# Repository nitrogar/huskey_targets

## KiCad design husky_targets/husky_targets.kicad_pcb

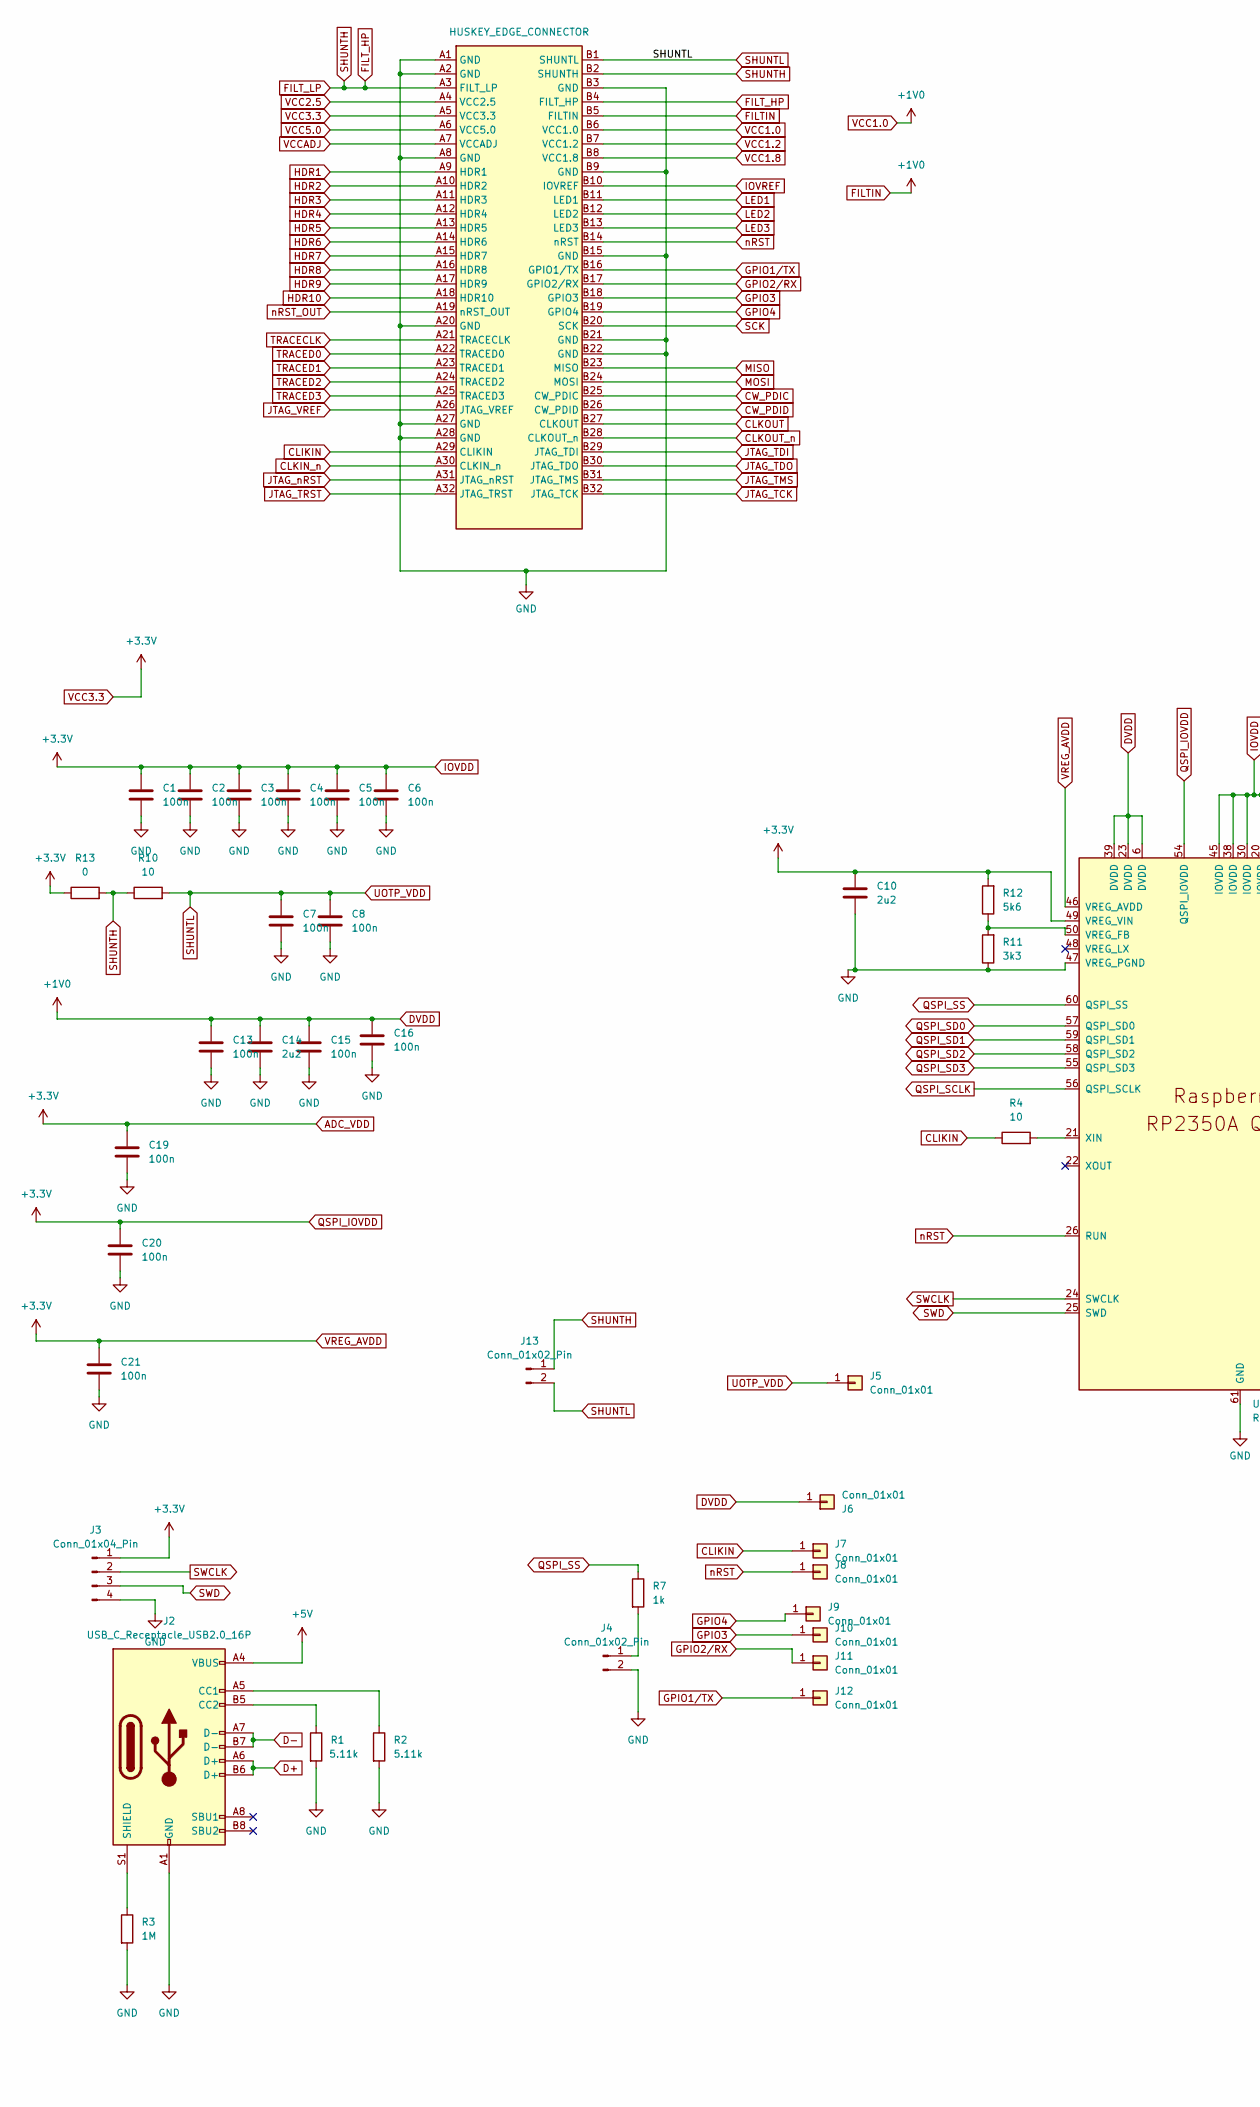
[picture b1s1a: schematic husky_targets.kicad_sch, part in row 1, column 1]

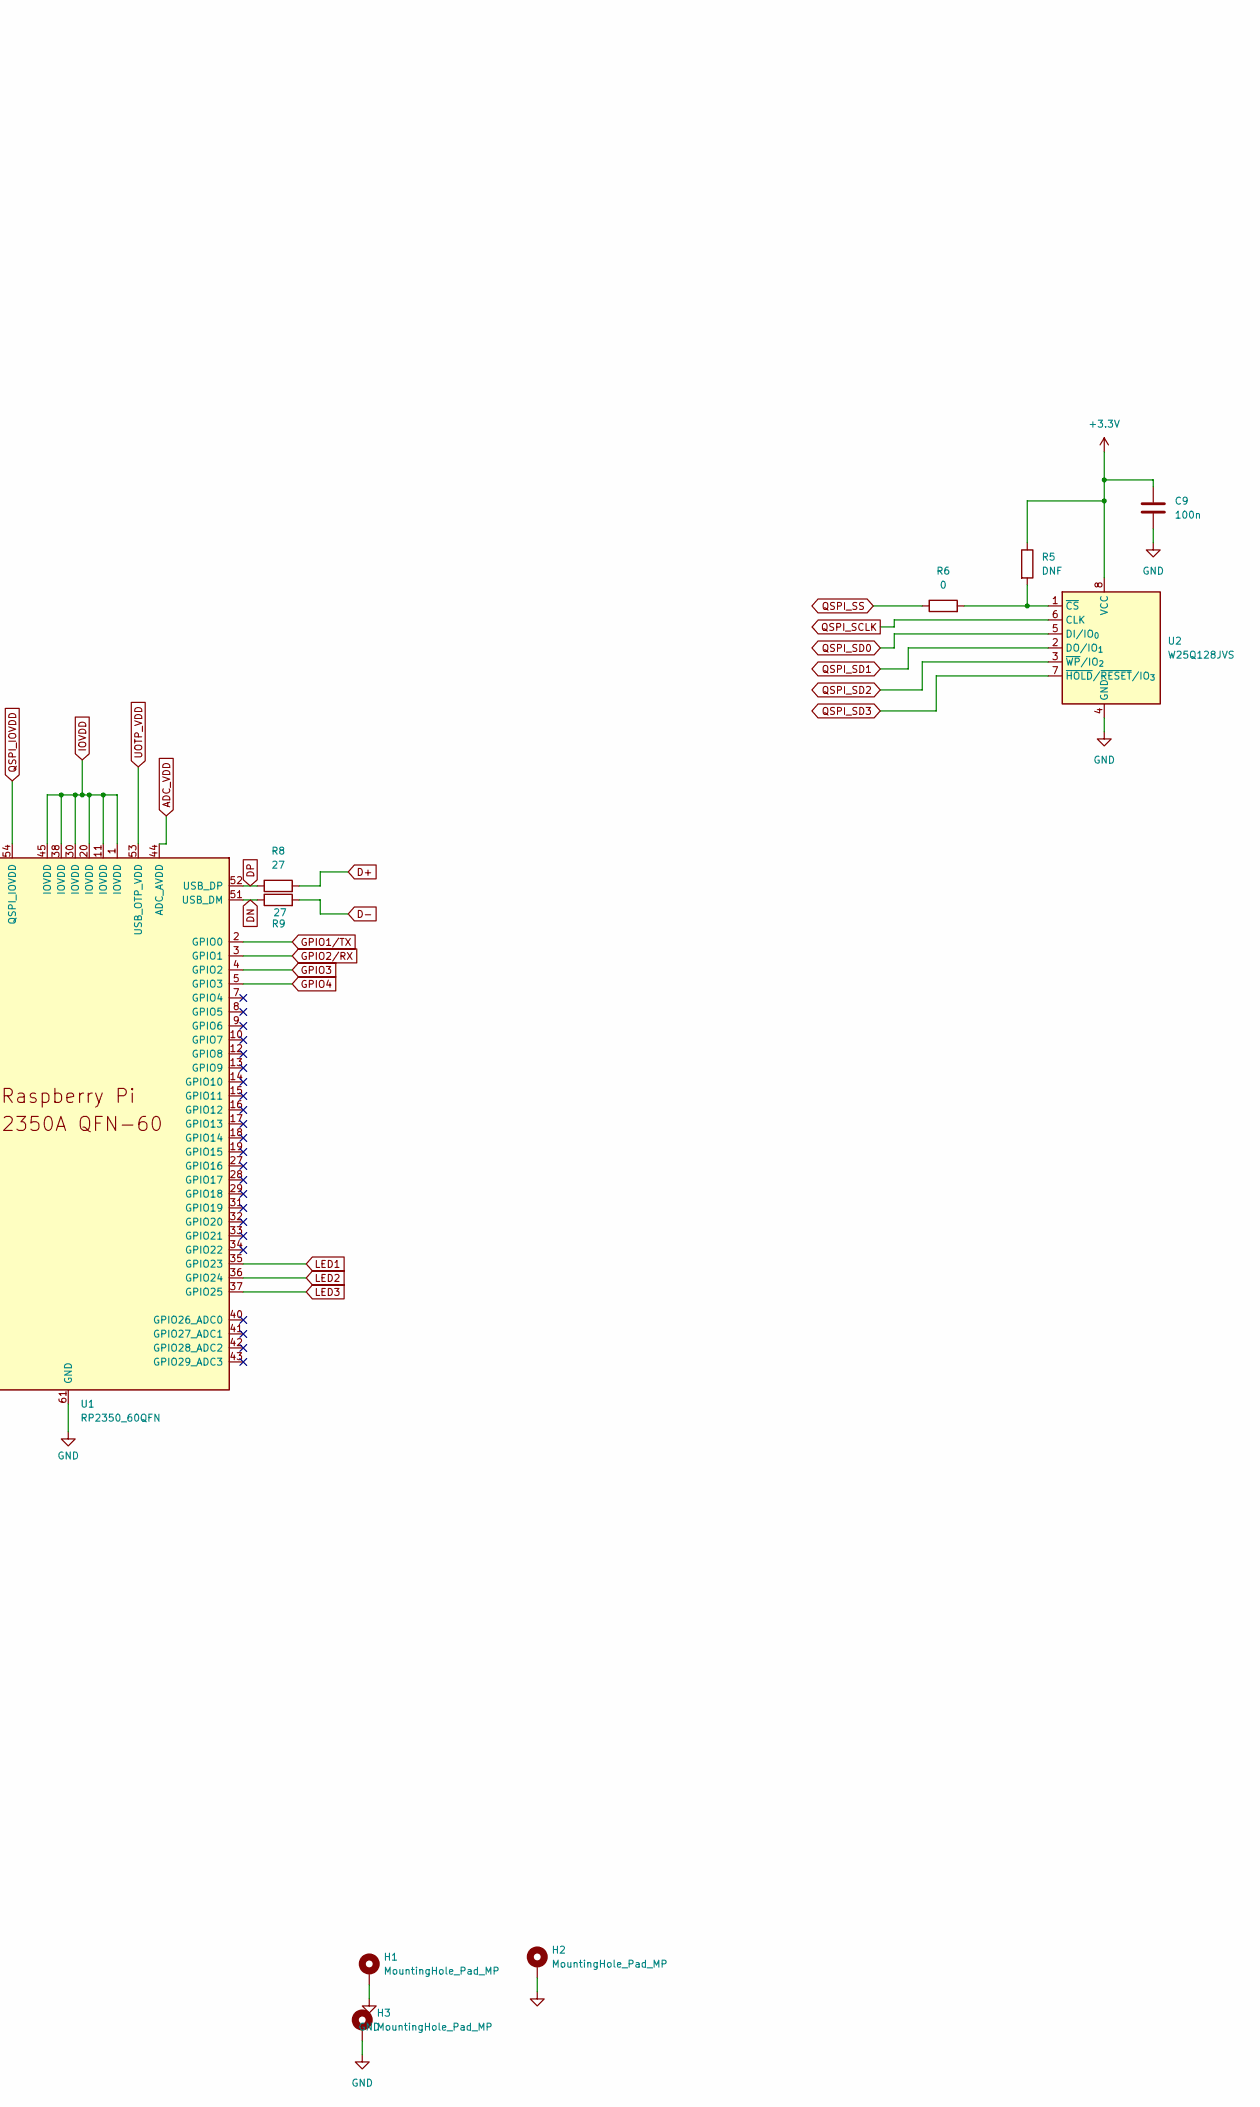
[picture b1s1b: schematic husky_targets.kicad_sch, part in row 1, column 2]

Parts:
C1, C2, C3, C4, C5, C6, C7, C8, C9, C13, C15, C16, C19, C20, C21: 100n; C_0603_1608Metric_Pad1.08x0.95mm_HandSolder
C10, C14: 2u2; C_0603_1608Metric_Pad1.08x0.95mm_HandSolder
H1, H2, H3: MountingHole_Pad_MP; MountingHole_2.2mm_M2_Pad_Via
J1: HUSKEY_EDGE_CONNECTOR; BUS_PCIexpress_x4
J2: USB_C_Receptacle_USB2.0_16P; USB_C_Receptacle_G-Switch_GT-USB-7010ASV
J3: Conn_01x04_Pin; PinHeader_1x04_P2.54mm_Vertical
J4, J13: Conn_01x02_Pin; PinHeader_1x02_P1.27mm_Vertical
J5, J6, J7, J8, J9, J10, J11, J12: Conn_01x01; PinHeader_1x01_P1.27mm_Vertical
R1, R2: 5.11k; R_0603_1608Metric_Pad0.98x0.95mm_HandSolder
R3: 1M; R_0603_1608Metric_Pad0.98x0.95mm_HandSolder
R4, R10: 10; R_0603_1608Metric_Pad0.98x0.95mm_HandSolder
R5: DNF; R_0603_1608Metric_Pad0.98x0.95mm_HandSolder
R6, R13: 0; R_0603_1608Metric_Pad0.98x0.95mm_HandSolder
R7: 1k; R_0603_1608Metric_Pad0.98x0.95mm_HandSolder
R8, R9: 27; R_0603_1608Metric_Pad0.98x0.95mm_HandSolder
R11: 3k3; R_0603_1608Metric_Pad0.98x0.95mm_HandSolder
R12: 5k6; R_0603_1608Metric_Pad0.98x0.95mm_HandSolder
U1: RP2350_60QFN; RP2350-QFN-60-1EP_7x7_P0.4mm_EP3.4x3.4mm_ThermalVias
U2: W25Q128JVS; SOIC-8_5.3x5.3mm_P1.27mm

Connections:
+5V: J2.A4 (VBUS), J2.A9 (VBUS), J2.B4 (VBUS), J2.B9 (VBUS)
ADC_VDD: C1.1, C2.1, C3.1, C4.1, C5.1, C6.1, C9.1, C10.1, C19.1, C20.1, C21.1, J1.A5 (VCC3.3), J3.1, R5.1, R12.2, R13.1, U1.1 (IOVDD), U1.11 (IOVDD), U1.20 (IOVDD), U1.30 (IOVDD), U1.38 (IOVDD), U1.44 (ADC_AVDD), U1.45 (IOVDD), U1.46 (VREG_AVDD), U1.49 (VREG_VIN), U1.54 (QSPI_IOVDD), U2.8 (VCC)
CLIKIN: J1.A29 (CLIKIN), J7.1, R4.1
CLKIN_n: J1.A30 (CLKIN_n)
CLKOUT: J1.B27 (CLKOUT)
CLKOUT_n: J1.B28 (CLKOUT_n)
CW_PDIC: J1.B25 (CW_PDIC)
CW_PDID: J1.B26 (CW_PDID)
D+: J2.A6 (D+), J2.B6 (D+), R8.2
D-: J2.A7 (D-), J2.B7 (D-), R9.2
DN: R9.1, U1.51 (USB_DM)
DP: R8.1, U1.52 (USB_DP)
DVDD: C13.1, C14.1, C15.1, C16.1, J1.B5 (FILTIN), J1.B6 (VCC1.0), J6.1, U1.6 (DVDD), U1.23 (DVDD), U1.39 (DVDD)
FILT_HP: J1.A3 (FILT_LP), J1.B2 (SHUNTH), J1.B4 (FILT_HP), J13.1, R10.1, R13.2
GND: C1.2, C2.2, C3.2, C4.2, C5.2, C6.2, C7.2, C8.2, C9.2, C10.2, C13.2, C14.2, C15.2, C16.2, C19.2, C20.2, C21.2, H1.MP, H2.MP, H3.MP, J1.A1 (GND), J1.A2 (GND), J1.A8 (GND), J1.A20 (GND), J1.A27 (GND), J1.A28 (GND), J1.B3 (GND), J1.B9 (GND), J1.B15 (GND), J1.B21 (GND), J1.B22 (GND), J2.A1 (GND), J2.A12 (GND), J2.B1 (GND), J2.B12 (GND), J3.4, J4.2, R1.2, R2.2, R3.2, R11.1, U1.47 (VREG_PGND), U1.61 (GND), U2.4 (GND)
GPIO1/TX: J1.B16 (GPIO1/TX), J12.1, U1.2 (GPIO0)
GPIO2/RX: J1.B17 (GPIO2/RX), J11.1, U1.3 (GPIO1)
GPIO3: J1.B18 (GPIO3), J10.1, U1.4 (GPIO2)
GPIO4: J1.B19 (GPIO4), J9.1, U1.5 (GPIO3)
HDR1: J1.A9 (HDR1)
HDR2: J1.A10 (HDR2)
HDR3: J1.A11 (HDR3)
HDR4: J1.A12 (HDR4)
HDR5: J1.A13 (HDR5)
HDR6: J1.A14 (HDR6)
HDR7: J1.A15 (HDR7)
HDR8: J1.A16 (HDR8)
HDR9: J1.A17 (HDR9)
HDR10: J1.A18 (HDR10)
IOVREF: J1.B10 (IOVREF)
JTAG_TCK: J1.B32 (JTAG_TCK)
JTAG_TDI: J1.B29 (JTAG_TDI)
JTAG_TDO: J1.B30 (JTAG_TDO)
JTAG_TMS: J1.B31 (JTAG_TMS)
JTAG_TRST: J1.A32 (JTAG_TRST)
JTAG_VREF: J1.A26 (JTAG_VREF)
JTAG_nRST: J1.A31 (JTAG_nRST)
LED1: J1.B11 (LED1), U1.35 (GPIO23)
LED2: J1.B12 (LED2), U1.36 (GPIO24)
LED3: J1.B13 (LED3), U1.37 (GPIO25)
MISO: J1.B23 (MISO)
MOSI: J1.B24 (MOSI)
unnamed: J2.A5 (CC1), R2.1
unnamed: J2.B5 (CC2), R1.1
unnamed: J2.S1 (SHIELD), R3.1
unnamed: J4.1, R7.2
unnamed: R11.2, R12.1, U1.50 (VREG_FB)
unnamed: R4.2, U1.21 (XIN)
unnamed: R5.2, R6.2, U2.1 (~CS)
QSPI_SCLK: U1.56 (QSPI_SCLK), U2.6 (CLK)
QSPI_SD0: U1.57 (QSPI_SD0), U2.5 (DI/IO_{0})
QSPI_SD1: U1.59 (QSPI_SD1), U2.2 (DO/IO_{1})
QSPI_SD2: U1.58 (QSPI_SD2), U2.3 (~WP/IO_{2})
QSPI_SD3: U1.55 (QSPI_SD3), U2.7 (~HOLD/~RESET/IO_{3})
QSPI_SS: R6.1, R7.1, U1.60 (QSPI_SS)
SCK: J1.B20 (SCK)
SHUNTL: C7.1, C8.1, J1.B1 (SHUNTL), J5.1, J13.2, R10.2, U1.53 (USB_OTP_VDD)
SWCLK: J3.2, U1.24 (SWCLK)
SWD: J3.3, U1.25 (SWD)
TRACECLK: J1.A21 (TRACECLK)
TRACED0: J1.A22 (TRACED0)
TRACED1: J1.A23 (TRACED1)
TRACED2: J1.A24 (TRACED2)
TRACED3: J1.A25 (TRACED3)
VCC1.2: J1.B7 (VCC1.2)
VCC1.8: J1.B8 (VCC1.8)
VCC2.5: J1.A4 (VCC2.5)
VCC5.0: J1.A6 (VCC5.0)
VCCADJ: J1.A7 (VCCADJ)
nRST: J1.B14 (nRST), J8.1, U1.26 (RUN)
nRST_OUT: J1.A19 (nRST_OUT)

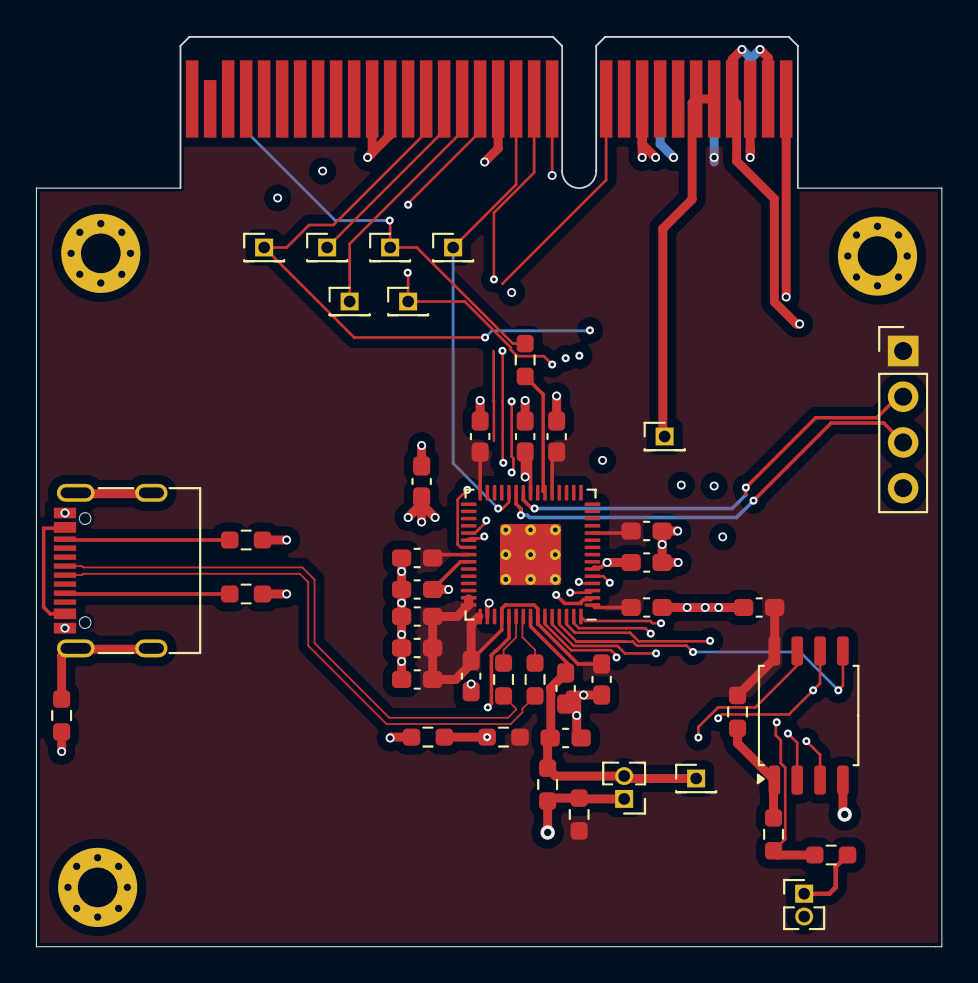
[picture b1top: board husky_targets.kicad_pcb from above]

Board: 4 copper layers, 50.3 x 50.5 mm, 48 parts (0 on the bottom side), 34 nets.

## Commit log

2025-04-19 adding gitignore
2025-04-19 adding rp2350; not complete
2025-04-28 finishing the schematic, starting with the layout
2025-04-28 done most of the pcb layout except the usb differntial pairs, well look for it later
2025-05-02 done first version of RP2350 OTPVDD board
2025-08-11 final final
